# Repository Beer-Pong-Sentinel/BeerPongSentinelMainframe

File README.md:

# Beer Pong Sentinel Project
This page contains a detailed description of the Beer Pong Sentinel project for the Engineering Physics capstone course at UBC.

## Our Team

|  |  |  |  |
|:-----------------------:|:------------------------:|:-------------------------:|:------------------------:|
| **Harry Hu**           | **Eldad Zipori**         | **Polina Shopina**        | **Brian Yan**            |
| [LinkedIn](https://www.linkedin.com/in/harrytyhu/) | [LinkedIn](https://www.linkedin.com/in/eldad-zipori-a411a5157/) | [LinkedIn](https://www.linkedin.com/in/polina-shopina/) | [LinkedIn](https://www.linkedin.com/in/brian-yan/) |

## Background
The inspiration for this project came from an innocent university game - beer pong.
We thought, “it would be pretty cool to build a robot that could intercept all of our opponent's shots”! 

Although we've pivoted away from ping pong balls to the larger and more predictable tennis balls, our goal remains the same: to prevent a target from reaching a zone at the edge of a table using an interception system.

### General Interception Process

The small animation shows the different high level stages our system has to take to intercept a ball.

First you see the general setup of our system, and it's different components. The remaining steps are as follows:
* our cameras detect a tennis ball in the air and triangulate its 3D location
* our cameras continue capturing frames until we have enough data to predict the target's trajectory
* we compute the predicted trajectory and based on our understanding of system latency, determine where along the trajectory to intercept the target
* we rotate our launcher in the altitude and azimuth directions
* we trigger the launcher to fire an interceptor at the right time

### Error, Latency, Jitter, and Uncertainty

The last error we need to account for is the error in the prediction itself. This comes from the differences in actual ball trajectories vs the trajectory we predict for them. To measure this simply compare  a trajectory of a ball from a video, to a predicted trajectory. Most of the work on this is done and can be found in (...).

Our estimates for all the errors are provided in the table below.
|Source| Symbol | Quantity | Units |Notes|
|----------|----------|----------|----------|----------|
|Prediction|Ep|N/A||Need to collect data|
|Integration|Ei|N/A||Need to collect data|
|Cameras|Ec|0.3-0.8|Pixels|Result of camera's triangulation|
|Motors - Azimuth|Eθ,azi|0.450|Degrees| Manufacturer data|
|Motors - Altitude|Eθ,alti|0.057|Degrees|Manufacturer data|
|Pneumatic Mechanism| Eθ,s|0.00485| Radians | Maximum measured spread|
|Electromechanical Jitter| Et|1.2|milliseconds| Maximum measured jitter| 

_Note_: The integration error Ei encapsulates the error in the cameras and the motors when trying to aim at a target after motor-calibration. It can be thought of as the shortest distance between a laser beam collinear with the launch barrel and a stationary target's centroid.

_Note_: Some values such as the integration error Ei are not calculated yet. Prediction is only theoretical as we did not fully integrate it. 

<!-- _Why have different units?_\
We would like to get the most accurate estimation for the maximum error in our system. For that reason we comply with the manufacturer choice of unit, and covert the units only when plugging into the final error estimation.  -->

<!-- _Note_: We are assuming the pallet travels at around the speed the manufacturer claims *131meters per seconds*. -->

### Interception Timeline
To truly understand this project you will need to understand the timeline in which the system operate. This might take a few seconds (or a few months).

The important thing to note here that prediction is implemented assuming worst-case latency for all processes. This means that the only jitter that affects our interception error is the electromechanical jitter in our triggering mechanism as we always wait a constant amount of time before firing.

<!-- Since the launcher provide a move done command, we recommend to always choose an interception point as if all jitter before the move done actually happens, this will cause the error in interception to come only from actions taken after the move done status (plus the error from the LUT itself.).

This makes the main challenge problem of interception the timing of the triggering itself. This is since all error's are measureable.  -->

## Electrical
### Layout

### Components
|Designation| Description | Part Number | Amount | Datasheet |
|----------|----------|----------|----------|----------|
|CM| Blackfly S Camera   | BFS-U3-04S2C-C  | 2   |[Teledyne](https://www.teledynevisionsolutions.com/products/blackfly-s-usb3/?model=BFS-U3-04S2C-C&vertical=machine%20vision&segment=iis)|
|MAZ| Stepper Motor   | CPM-SDSK-3421S-RLN  | 1   |[Teknic](https://teknic.com/model-info/CPM-SDSK-3421S-RLN/?model_voltage=48VDC)|
|MAL|SDK Motor   | CPM-SCSK-3411S-ELNB  | 1   |[Teknic](https://teknic.com/model-info/CPM-SCSK-3411S-ELNB/?model_voltage=75)   |
|PS1| Motor Power Supply | IPC-5 | 1 | [Teknic](https://teknic.com/products/servo-motor-dc-power-supply/)|
|PS2| 24VDC Power Supply | SE-450-24 | 1 |[Mouser](https://www.mouser.ca/ProductDetail/MEAN-WELL/SE-450-24?qs=M1W9nuUSIjpXT24%252B6%252BDJCg%3D%3D&srsltid=AfmBOoo0Gw3eBcZ0qDYIleJDajS5qSaI-gmjeNrVGrdYgwfqYw6543Ys)|
|SC| Motor Control Hub   | SC4-HUB  | 1   |[Teknic](https://teknic.com/sc4-hub/)   |
|SL| 12V Solenoid 42N   | 10MM JF-1253B   | 1   |[ Lee's Electronics](https://leeselectronic.com/en/product/4408-12v-solenoid-42n-10mm-jf-1253b.html)   |
|TC - N/A| Voltage regulator   | LM7805   | 1  | [Texas Instruments](https://www.ti.com/lit/ds/symlink/lm340.pdf)   |
|TC - D2| Diode    | 1N4007   | 1   | [Vishay](https://www.vishay.com/docs/88503/1n4001.pdf)   |
|TC - Q1| MOSFET    | IRF540   | 1   | [Vishay](https://www.vishay.com/docs/91021/irf540.pdf)   |
|TC - Q2/Q3| BJT    | 2N3904   | 2   | [Onsemi](https://www.onsemi.com/download/data-sheet/pdf/2n3903-d.pdf)   |

### Connections
| Designation | Description | Part Number  | Amount | Link|
|----------|----------|----------|----------|----------|
| MPC | Motors Power Cable | CPM-CABLE-PWR-MS120  | 2 | [Teknic](https://teknic.com/cpm-cable-pwr-ms120/) |
| MDC | Motors Data Cable | CPM-CABLE-CTRL-MU120  | 2 | [Teknic](https://teknic.com/CPM-CABLE-CTRL-MU120/) |
|PSC| Power Supply Cable| IPC35-CABLE110 | 1 |[Teknic](https://teknic.com/ipc35-cable110/)|
|HR10| Camera GPIO Cable| HR10A-7P-6S | 1 |[Teledyne](https://www.teledynevisionsolutions.com/products/hirose-hr10-6-pin-circular-connector/)|
|C1| USB-A to USB-B|  | 2 ||
|C2| Micro USB to USB-B/C|  | 2 ||
|C3| 2-pin Molex to Ring Connector | |2||
|C4| USB3 to Micro-B | |2||
|SJ| Jumber Wire|  | 2| | 

### Solenoid Control Circuit
_Note:_ The physical circuit in the current setup of the project is not the printed PCB, but a breadboard version without the option for a manual control and a 5V voltage regulator that steps down the 24V for the solenoid.

The full KiCAD design for the solenoid control PCB can be found inside `sol_ctrl_pcb`.

## Mechanical 
 
The original BB gun we got for this project is the [Crosman R1 Full-Auto - Black](https://www.crosman.com/product/crosman-full-auto-r1-black-bb/).\
The pneumatic mechanism requires two [12-gram Powerlet CO2 Cartridges](https://www.crosman.com/product/crosman-12-gram-powerlet-co2-cartridges/).\
This magazine uses [4.5mm copper pellets](https://www.crosman.com/product/crosman-copperhead-bbs/).

### Safety

When testing or operating the BB gun pneumatic mechanism/especially in a closed room, make sure to wear face protection. The pellets are copper and tend to bounce around. This will happen after a while even if you have a cardboard stack target. 

*To learn more about safety and replacing gas cartridges:* head to the `safety` folder and read about safety of operating the BB gun in testing locations and how to safely replace the gas cartridges for the pneumatic mechanism. 

### Launcher Modifications

The main rational behind modifying the original BB gun is to reduce the mass, size, and moment of inertia to allow up to actuate our launcher with ease. A larger, weirdly shaped, launcher would have required much more expensive motors and a more rigid design for the launcher mounts. 

### Launcher's Moment of Inertia
Calculating the moment of inertia for the launcher plays a key role in the design and motor selection.

The below figure shows our CAD model of the launcher with its mechanical parameters. The marker/arrows indicate the mounting location for the launcher.

The launcher's model was built by weighting its various components and recreating the rough or exact shapes of its components. The result parameter should be considered as a lower bound. We recommend using a factor of safety of 1.5 at least in any calculations that include these parameters.

[Onshape link for the launcher model](https://cad.onshape.com/documents/76652a767c23fe435988178b/w/9803612b38e4d7d0dd289d8c/e/d43adc66a7cc15ee7d39c4dd?renderMode=0&uiState=67d88cabb3e65b43110218b9)

### Motor Selection
To select motors we ran simulations of motion profiles using both the inertia of our launcher and the rotor inertia of some promising motors. 
We simulate both a triangular motion profile, which assumes instant change from acceleration to de-acceleration, and a trapezoidal motion profile, which assumes equal time in acceleration, operation in max acceleration, and deceleration. 

<!-- While both are not perfect and can be improved, by giving assuming less time in max acceleration for example, they give us a good idea of the torque and velocities we will need to operate in to actuate our launcher.  -->

The model takes the following parameters:
```python
object_inertia 
motor_inertia 
theta_target 
time_window
safety_factor
```

We recommend being conservative with the safety factor to account for imperfections in tuning, inertia calculations, and motion profile control.
An example of such triangular motion profile can be seen below. 

_Note_:\
Something we learned in the hard way is that the rotor inertia should match the inertia of the load it drives. This mostly affects tuning the motor. In the case it does not match, you might want to gear the motor. This is not ideal as it will cause a loss in resolution of the encoder, but will provide better tuning. 

_Our problem_:\
Specifically with the motors we are using we found out that our altitude motor (SDK controlled) does not allow to limit the velocity for tuning. This causes the motor to saturate in torque and to produce sub-optimal tuning. To mitigate this, we created a program in our software to map the time it take to move to an angle with a certain velocity limit. Creating a map of `(velocity, angle)` to `(time taken)`. We can use this to find the optimal maximum velocity to use to minimize the time it takes to go to any given angle. 

These profiles can be ran for any internal parameters you can change in the motor. We only found that you can change the Jerk and the "Fine-tuning" (how stiff/quite the motor moves) in our altitude (SDK controlled) motor. 

Such motion profiles with different jerk control settings are shown below (the graphing script can be found at [./motors/Altitude Time Motion Profile Visualization.ipynb](https://github.com/Beer-Pong-Sentinel/BeerPongSentinelMainframe/blob/main/motors/Altitude%20Time%20Motion%20Profile%20Visualization.ipynb)). 

From this analysis, we determined that using no jerk control and a velocity limit of 20 RPM produces the optimal jerk and latency over our range of possible altitude angles.

### Motor Tuning
Both motors need to to be tuned with ClearPath (azimuth) and ClearView (altitude). The tuning we are using can be found under the [./motors](https://github.com/Beer-Pong-Sentinel/BeerPongSentinelMainframe/tree/main/motors) folder with the timestamp and description.

_Important Last Minute Note:_ We found out that the calibration files are readable! That means that you can tune the motor by changing their parameters. A sub-project for this will be to make your own tuning program that will limit the velocity of the altitude motor and tune it well (though this is more Teknic's job).
### Components

| Description | Part Number  | Amount | Link|
|----------|----------|----------|----------|
| Timing Belt Pulley 1.500" OD, for 1/2" Shaft Diameter | 6495K752  | 2 | [McMaster](https://www.mcmaster.com/6495K752/) |
| Rotary Shaft 1/2" Diameter, 6" Long | 4149N15  | 1 | [McMaster](https://www.mcmaster.com/4149N15/) |
| Ball Bearing for 1/2" Shaft Diameter |60355K173| 3 |[McMaster](https://www.mcmaster.com/60355K173/)|
| Series Timing Belt| 6484K226 | 1 |[McMaster](https://www.mcmaster.com/6484K226/)|
|  Dry-Running Nylon Sleeve Bearing Flanged, for 1/2" Shaft Diameter and 3/4" Housing ID, 7/16" Long| 6389K233 | 2 |[McMaster](https://www.mcmaster.com/6389K233/)|
| Carbon Steel Wide-Rim Ring, 0.048" Thick x 1/2" ID x 7/8" OD| 97669A200 | 1 (pack of 25) |[McMaster](https://www.mcmaster.com/6389K233/)|

### Launcher Mount and Maneuvering
_Click to open OnShape CAD model_
|  | | |
|----------|----------|----------|
### Assembly 

## Firmware
The full firmware project can be found in the `firmware` folder. Our firmware runs on an Arduino Uno with the following pins connected. 

### Firmware Parameters
**_Solenoid Pulse Width:_**\
Location: firmware\
Variable: TRIGGERING_DELAY\
Scale: Miliseconds\
Current Settings: 75\
Considerations: 
- Time needs to be enough to allow for the solenoid to provide enough force to open the CO2 valve.
- Time should be too long as it wastes CO2.

**_Step Signal Pulse Width:_**\
Location: firmware\
Variable: AZI_DELAY\
Scale: Microseconds\
Current Settings: 100\
Considerations: 
- Minimum specification of motor control must be met
- Rise/fall time affect on the pulse
- Motor minimum control voltage is 5V
- Effect on motion profile; how steps in certain frequencies translate to different velocities

_Note:_ Currently this sets both the pulse width and the frequency of pulses as the high time and low time are symmetric. This can be changed.

**_Azimuth Motor Settlement Range:_**\
Location: ClearPath MSP\
Access: Advanced -> High-Level Feedback (HLFB) Setup -> In-Range Position Window (ctns)\
Current Settings: 1\
Notes: Current HLFB Output setting is All System Go (ASG) - Position\
Considerations: 
- Azimuth motor has a smaller encoder resolution than altitude
- See altitude considerations

**_Azimuth Motor Settlement Delay:_**\
Location: ClearPath MSP\
Access: Advanced -> High-Level Feedback (HLFB) Setup -> Verify Time (ms)\
Current Settings: 10.1\
Notes: Current HLFB Output setting is All System Go (ASG) - Position\
Considerations: 
- Azimuth motor tuning runs better the altitute
- See altitude considerations

**_Altitude Motor Settlement Range:_**\
Location: ClearView\
Access: Details -> Move Status Indicators... -> In-Range Position Window (ctns)\
Current Settings: 5\
Considerations:
- We have some tolerance for error so we can settle within some range of the encoder ctns
- Moving faster might take priority.

**_Altitude Motor Settlement Delay:_**\
Location: ClearView 
Access: Details -> Move Status Indicators... -> Verify Time (msec)\
Current Settings: 10.1\
Considerations:
- Move done might given more than once if the launcher oscillates around a point.
- More delay means more latency before we can trigger.

## Camera system

### Camera's Parameters
The full camera parameters can be found under `/simulations` and `data analysis/Camera Calculations.xlsx`.
This provides the full details of all the intrinsic parameters of the [BFS-U3-04S2C-C]((https://www.teledynevisionsolutions.com/products/blackfly-s-usb3/?model=BFS-U3-04S2C-C&vertical=machine%20vision&segment=iis)) cameras we are using, inluding some that require calculations. 

### Intrinsic/Extrinsic Calibration 

We use stereo calibration to to correct for lens distortions and determine the precise relative placement of two cameras. We use a printed chessboard pattern of known dimensions and take images at various positions and orientations. By analyzing these images, the calibration algorithm uses the known geometry of the chessboard to first estimate and correct each camera’s intrinsic parameters, “undistorting” the images. It then compares corresponding points in both camera views to determine the cameras’ relative positions and orientations. These calibration results, which include both the intrinsic corrections and the extrinsic parameters describing how the cameras are arranged, can be combined into a projection matrix that enables the reconstruction of a 3D point using an image from each camera.

You can find some calibration data under [./calibration data](https://github.com/Beer-Pong-Sentinel/BeerPongSentinelMainframe/tree/main/clibration data) . As long as the orientation of the two cameras with respect to each other does not change you might not need to re-calibrate. Note that under most new environments it is recommended to recalibrate.
### Color Detection
Initially we tried to detect a static target (tennis ball) using conventional methods such as HSV/RGB thresholding. 
This turned out to be more challenging than we thought, as the camera resolution is only 720x540.

While colors seem green, or red, to us, it is very clear in processing that a tennis ball contains a lot of non-green content. 
To fix this we tried a few things:
- Putting a black curtain in the background to more easily see the green tennis ball
- Increasing the saturation on the cameras making most of the view look red, but making green more clear to distinguish
- We used clear, consistent lighting that does not flicker and turned off all the other light sources in the room.

In order to intercept the ball at some point along its trajectory, we need to triangulate its position across 3D space both quickly and accurately. However, to triangulate the position of the ball, we need to determine the pixel coordinates of the center of the ball for each image from our two cameras. Thus, we need a robust image processing pipeline that can efficiently and consistently retrieve the centroid of a ball from an image.

We constructed the Ball Detection pipeline to accomplish this task which works as follows:

1. First, apply an HSV threshold to the image, which highlights only objects within a certain hue, saturation, and value range. 
2. Next, apply a MOG2 background subtraction to identify any moving objects in the image. 
3. Combine these two outputs in order to retrieve only moving objects which match the specified colors defined by the HSV range. 
4. Once combined, apply a dilation and erosion process to remove any noise. The final image should contain only highlighted pixels that match the position of the ball.
5. Lastly, find the centroid of the highlighted pixels for both camera's and pass these values to the triangulation function to determine the position of the ball in 3D space.

To read more about HSV and RGB thresholding, see [OpenCV's official documentation](https://docs.opencv.org/3.4/da/d97/tutorial_threshold_inRange.html).

### Yolo-OpenCV Object Detection 
Eventually, we decided to use a deep neural network (DNN) for static ball detection. While our final goal is prediction of a moving target, we require this to be able to demo our camera-launcher calibration, and to be able to give an estimation of its error.

YOLO is an open source model for object detection. It is extremely easy to use and has very impressive performance. We are using *YOLOv8*, for compatibility and reliability.

Read more about [YOLO in the official site](https://docs.ultralytics.com/).

To train our YOLO model we simply found [a dataset](https://universe.roboflow.com/alexa-wpmns/tennis-ball-obj-det/dataset/8) that looked promising to us and worked well when we tested it online.
We found a dataset with 4725 annotated images of tennis balls. 

<!-- The important part for this is that high precision, and the images were not only in a tennis court (which would probably not be so good for detecting a tennis ball in a general environment). -->

Training the model itself is straightforward and was done using a CLI.After training, we converted the trained model to ONNX format and loaded it into OpenCV’s DNN module, as C++ does not have a native YOLO library.\
[How to train a YOLO model](https://docs.ultralytics.com/modes/train/#usage-examples)\
[Read more about OpenCV DNN](https://docs.opencv.org/4.x/d2/d58/tutorial_table_of_content_dnn.html)

From this point onwards, we also wanted to utilize a dedicated GPU to do our image processing as fast as possible. For this we had to build OpenCV with CUDA nodes for DNN.\
[You can find how to build OpenCV and CUDA here](https://medium.com/@amosstaileyyoung/build-opencv-with-dnn-and-cuda-for-gpu-accelerated-face-detection-27a3cdc7e9ce)

### Cameras-Launcher calibration

To convert from a predicted point in 3D space to motor positions for interception, we require launcher-camera calibration. We accomplished this using a look-up table, which is created as follows. After placing a large surface in front of the launcher and attaching a laser pointer collinear with the barrel, we can move to a number of motor positions and record the 3D location of the laser dot on the surface. After repeating the process with the same motor positions and a surface further away from the launcher, we can connect the dots to obtain a vector and origin for each motor position. Because this becomes a lengthy process when collecting data for a fine grid, we can instead interpolate to approximate the vectors and origins we would see if we collected more data.

The process of converting from 3D coordinates to motor positions then becomes simple: we compute the distance between the desired 3D coordinate and each vector in the interpolated dataset. Then, we can simply read off the motor positions for the shortest distance. 

Ideally, the surfaces are placed such that the expected position of interception lies between them and that the angles swept over encompass all viable angles for interception. Having the surfaces further apart reduces uncertainty in the vector directions, although this means that surface size also has to increase. 

The main advantage of this method over others is that it does not assume much from the system (such as that the launcher has spherical symmetry, the surfaces are flat, etc.), making it robust. The main disadvantage is the time required to do such a calibration, which has to be redone whenever the position of the cameras changes relative to the launcher or each other.

We did not have the time to collect extensive test data for this approach but we found that collecting a 20x20 grid of data with altitude angles from 0 to 15 degrees and azimuth angles from -15 to 15 degrees, interpolated to 60x60 grid of data, we were able to measure an average error of 37 millimetres from the center of the target from initial tests.

You can find a full simulation for this calibration that was done prior to implementing it under [./simulations and data analysis/Laser_Cal_Sim.ipynb](https://github.com/Beer-Pong-Sentinel/BeerPongSentinelMainframe/blob/main/simulations%20and%20data%20analysis/Laser_Cal_Sim.ipynb) to see how we came up with this idea for calibration, including some estimations for the error it might have.

## Software - System Control and GUI
We developed a GUI using Qt in C++ to facilitate subsystem and integration testing.
The full project for the software can be found under [./system control gui](https://github.com/Beer-Pong-Sentinel/BeerPongSentinelMainframe/blob/main/system control gui).
### Dependencies 
- Qt 6.8.0 or 6.8.3 (we used [Qt Creator](https://www.qt.io/product/development-tools))
- [Spinnaker SDK](https://www.teledynevisionsolutions.com/products/spinnaker-sdk/)
- OpenCV Built with [Nvidia DNN](https://developer.nvidia.com/cudnn)
- [Teknic SDK](https://teknic.com/downloads/)
- [Eigen C++](https://eigen.tuxfamily.org/index.php?title=Main_Page)

### Programs
#### Motor Control

This section provides a simple interface for enabling, moving, and disabling the azimuth and altitude motors. This allows to user to make sure both motors are properly connected. 

"Test Move Time" runs a script that iterates the altitude motor through a range of angles, repeating for a range of maximum velocities. The `(angle, velocity limit, time)` values are recorded in `altitude_time_test_dat.csv` within the Qt build folder.

#### Chessboard Calibration

This tab lets the user capture images to use for stereo calibration. We recommend taking 20-30 images where each corner of the chessboard is visible in both cameras. It is important that the camera feed on the left always corresponds to the camera physically on the left. If the cameras have not been moved relative to one another since another stereo calibration, the calibration can be loaded from a saved file.

#### Lookup Table Construction (Camera-Motor Calibration)

This tab is used to generate a lookup table for camera-motor calibration. To do this, 
1. Select the correct ports for the azimuth and altitude motors.
2. Enable the motors and ensure that they can be moved.
3. Place a surface some some distance away from the launcher.
4. Insert a laser pointer collinear to the barrel.
5. Set the upper and lower azimuth and altitude angles such that the laser points to the edge of the surface at those angles.
6. With "Far Sweep" selected, press "Sweep", wait for the sweep to conclude, and check "Far Sweep Done".
7. Move the surface closer to the launcher, and repeat the process for the near sweep.
8. Press "Calculate Lookup" to generate the lookup table.

If the position of two cameras relative to each other and the launcher hasn't changed since the last calibration, the calibration can be loaded from a saved file.

#### Ball Detection (TODO)

## Prediction

Prediction is one of the central tasks of our project. We know our trajectory is going to be approximately parabolic, which allows us to use classical physics to create a prediction for the trajectory of the ball.

The full work for the different methods of prediction we test can be found under [./simulation and data analysis/PredictionSimulation.ipynb](https://github.com/Beer-Pong-Sentinel/BeerPongSentinelMainframe/tree/main/simulations%20and%20data%20analysis/PredictionSimulation.ipynb)
Under the [./simulation and data analysis/data](https://github.com/Beer-Pong-Sentinel/BeerPongSentinelMainframe/tree/main/simulations%20and%20data%20analysis/data) folder you can find data that we used for our trajectory simulation. This data can be extracted from our GUI.
We used real data we captured from our full camera setup in order to compare the predicted trajectory to a real life trajectory. 

### Gravity Calibration
To be able to predict accurately, we cannot just assume that gravity points down in our camera coordinates. To produce a gravity vector, we simply take a few videos with our camera system of us letting go off a ball. We then process this data to find the gravity vector, and to estimate the value that we are observing for gravity. This provides much more accurate results than just assuming gravity is 9.8 m/s.

The code we use to estimate the gravity vector can be found under [./simulations and data analysis/GravityEstimation.ipynb](https://github.com/Beer-Pong-Sentinel/BeerPongSentinelMainframe/tree/main/simulations%20and%20data%20analysis/GravityEstimation.ipynb).
## Our System In Real Life

### Launcher - Beerie

### Integration Box
Our full integrated circuitry connects all components together through a single hub USB hub for a simple connection.
Labels and markers, with detailed diagrams, make setting up quick and simple.

### Cameras Setup
Our cameras are situated high with each 22.5 degree angle offset from their mounting point. This is done to capture a large range of view. We use high-power halogen lights to make sure the target is well lit at all times. These lights do not flicker which helps with background subtraction.

### Calibration Chessboard
Our 80cm x 60cm calibration chessboard is sandwiched between two acrylic plates, making it as flat as possible. 

### Aiming/Look up table calibration

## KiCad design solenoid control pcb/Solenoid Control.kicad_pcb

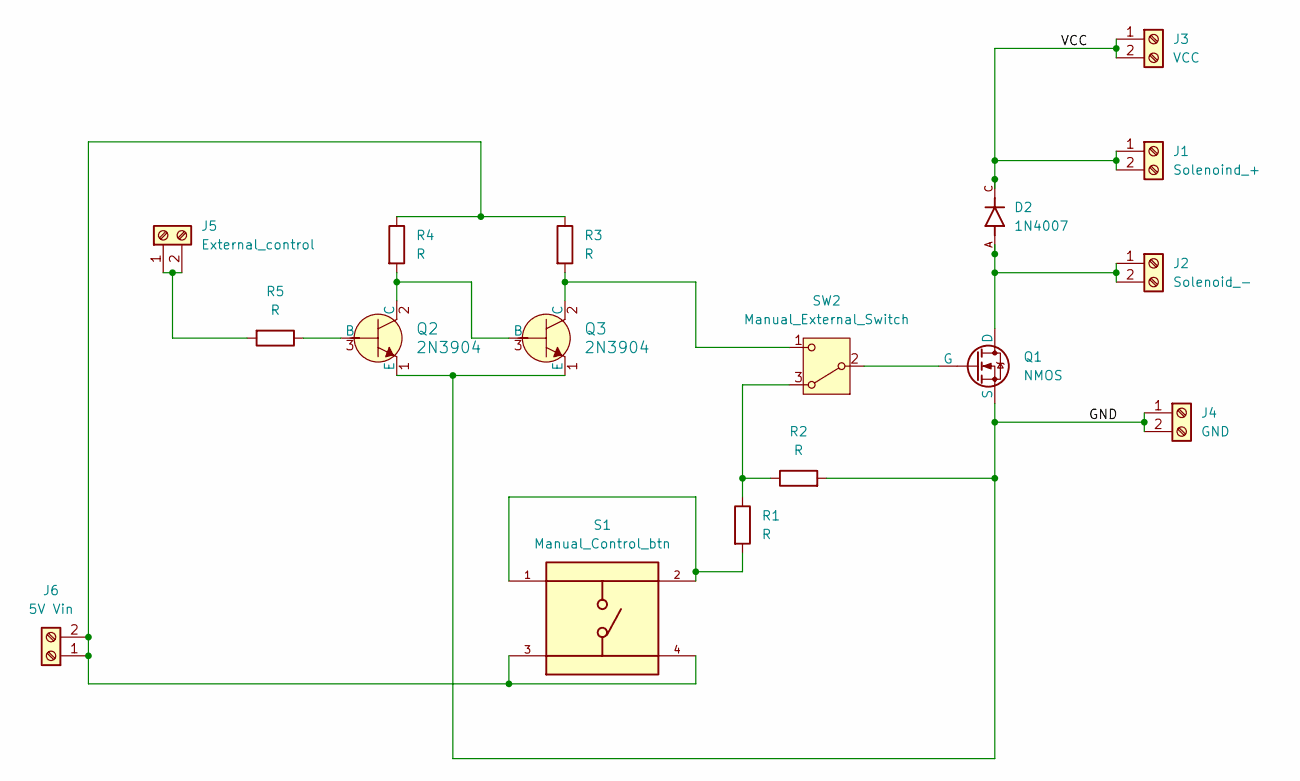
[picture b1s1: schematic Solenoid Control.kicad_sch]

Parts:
D2: 1N4007; DIOAD1060W80L520D270; PARTREV G
J1: Solenoind_+; TerminalBlock_TE_282834-2_1x02_P2.54mm_Horizontal
J2: Solenoid_-; TerminalBlock_TE_282834-2_1x02_P2.54mm_Horizontal
J3: VCC; TerminalBlock_TE_282834-2_1x02_P2.54mm_Horizontal
J4: GND; TerminalBlock_TE_282834-2_1x02_P2.54mm_Horizontal
J5: External_control; TerminalBlock_TE_282834-2_1x02_P2.54mm_Horizontal
J6: 5V Vin; TerminalBlock_TE_282834-2_1x02_P2.54mm_Horizontal
Q1: NMOS; TO254P1024X444X1989-3
Q2, Q3: 2N3904; TO-92L; MPN 2N3904
R1, R2, R3, R4, R5: R; R_Axial_DIN0207_L6.3mm_D2.5mm_P10.16mm_Horizontal
S1: Manual_Control_btn; SW_TS02-66-50-BK-160-LCR-D; PARTREV 1.0
SW2: Manual_External_Switch; SW_Slide-03_Wuerth-WS-SLTV_10x2.5x6.4_P2.54mm

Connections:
/GND: J4.1, J4.2, Q1.3 (S), Q2.1 (E), Q3.1 (E), R2.2
/VCC: D2.C, J1.1, J1.2, J3.1, J3.2
unnamed: D2.A, J2.1, J2.2, Q1.1 (D)
unnamed: J5.1, J5.2, R5.2
unnamed: J6.1, J6.2, R3.1, R4.1, S1.3, S1.4
unnamed 5: Q1.2 (G), SW2.2 (B); also elsewhere on the board
unnamed: Q2.3 (B), R5.1
unnamed: Q2.2 (C), Q3.3 (B), R4.2
unnamed 8: Q3.2 (C), R3.2, SW2.1 (C); also elsewhere on the board
unnamed: R1.2, S1.1, S1.2
unnamed 10: R1.1, R2.1, SW2.3 (A); also elsewhere on the board

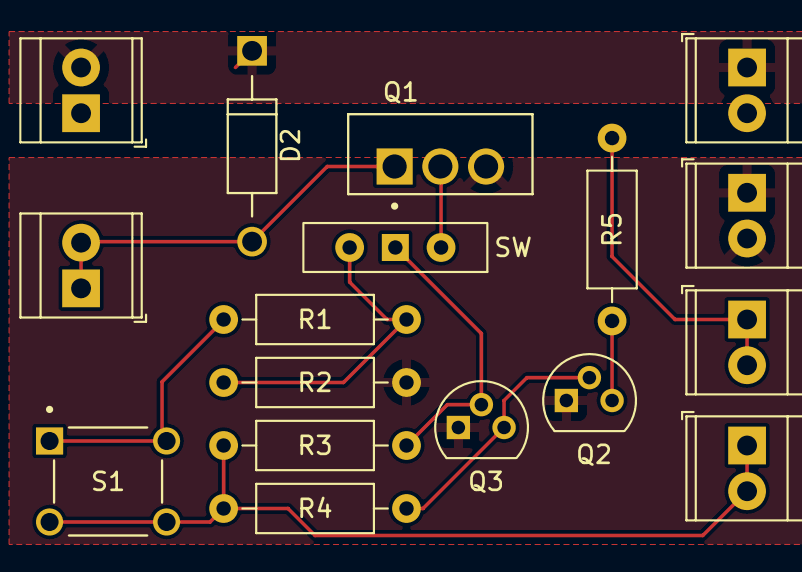
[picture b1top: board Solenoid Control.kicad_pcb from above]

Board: 2 copper layers, 17 parts (0 on the bottom side), 11 nets.

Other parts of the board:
SW: Manual_External_Switch; SW_Slide-03_Wuerth-WS-SLTV_10x2.5x6.4_P2.54mm

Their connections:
unnamed 5: SW.2 (B); also elsewhere on the board
unnamed 8: SW.1 (C); also elsewhere on the board
unnamed 10: SW.3 (A); also elsewhere on the board

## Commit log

2025-03-09 Create
2025-03-09 add elec layout
2025-03-12 firmware update
2025-03-12 testing underscore etc
2025-03-12 add electric design
2025-03-12 fix firmware figure
2025-03-12 try new line
2025-03-12 update electric layout
2025-03-12 update layout
2025-03-12 readme update
2025-03-17 Rename elec_layout.png to elec_layout_.png
2025-03-25 adding stuff
2025-03-25 table update
2025-03-25 background info
2025-03-26 more updates
2025-03-26 update inertia
2025-03-26 rename folder
2025-03-26 add visualization
2025-03-26 typo
2025-03-27 launcher info and procedures
2025-03-27 correct image to link
2025-03-27 altitude motor stuff
2025-03-27 correction
2025-03-27 Components
2025-03-27 small fix
2025-03-27 fix one result
2025-03-28 add titles
2025-03-28 spelling
2025-03-28 some firmware parameters
2025-03-28 add launcher
2025-03-28 bleh
2025-03-28 fix format
2025-03-29 motor stuff
2025-03-29 Formatting
2025-03-31 camera stuff
2025-03-31 yap about prediction error
2025-04-01 camera parameters
2025-04-01 prediction stuff
2025-04-01 more simulations
2025-04-01 camera paramete talbe
2025-04-01 some camera stuff
2025-04-02 new data things
2025-04-02 rename
2025-04-02 yap motor tuning
2025-04-02 remove empty column
2025-04-02 Some prediction yapping
2025-04-02 remove space
2025-04-02 gui stuff
2025-04-02 added team section
2025-04-02 added team pictures
2025-04-02 adding prediction stuff
2025-04-02 added ball detection stuff
2025-04-02 ball detection stuff
2025-04-02 format
2025-04-02 gravity stuff
2025-04-02 update pictures
2025-04-02 spellcheck
2025-04-03 GUI explanations
2025-04-03 move team up
2025-04-03 add calibration data
2025-04-03 text about lights
2025-04-03 update latency figure
2025-04-03 add gui
2025-04-16 added to launcher-camera calibration section
